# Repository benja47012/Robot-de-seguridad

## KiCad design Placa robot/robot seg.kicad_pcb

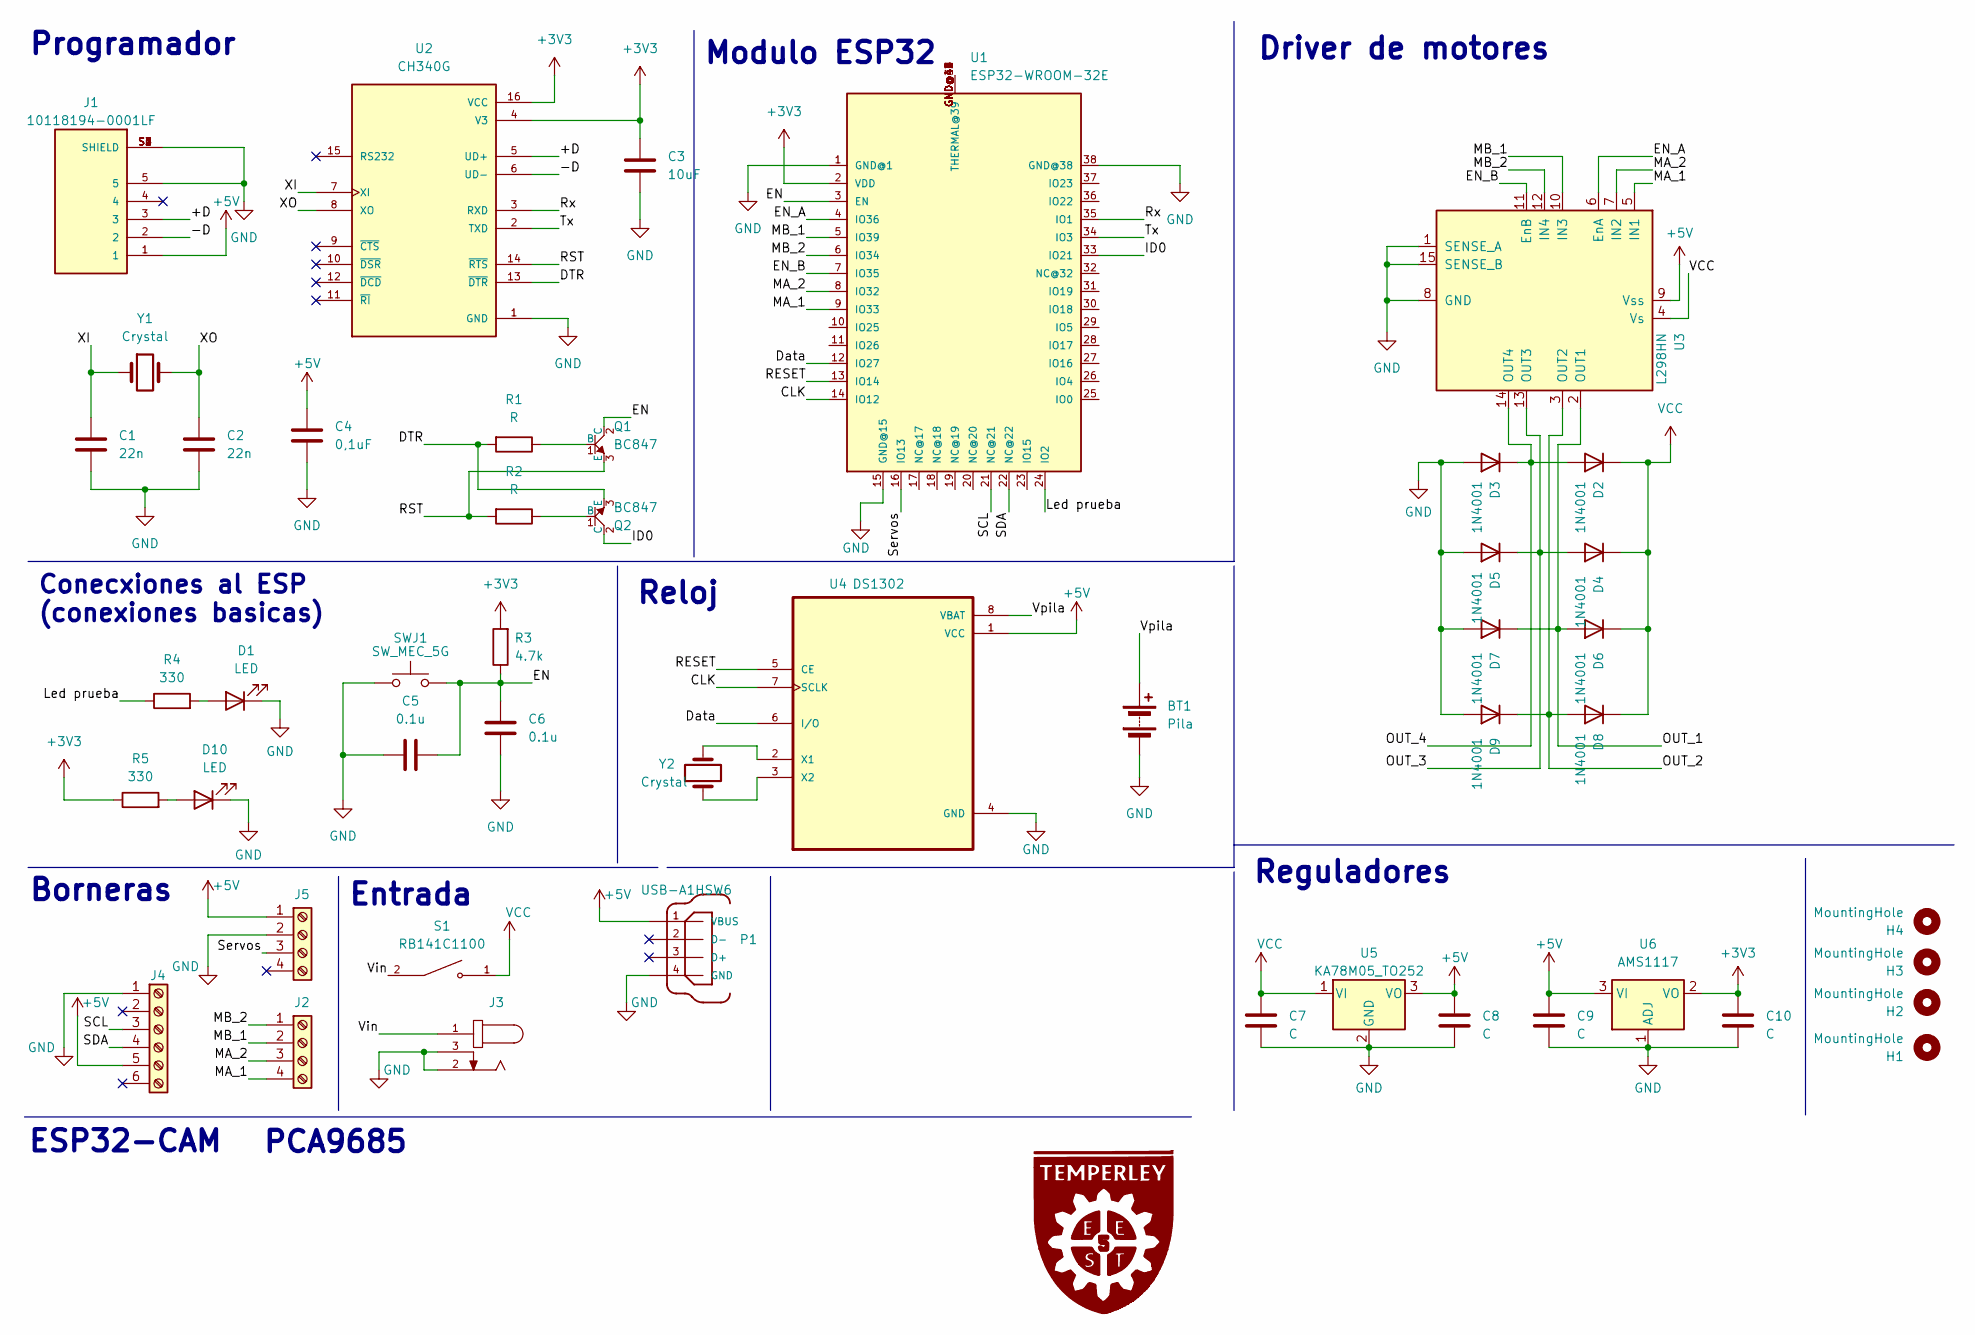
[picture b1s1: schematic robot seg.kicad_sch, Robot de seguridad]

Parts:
BT1: Pila; BatteryHolder_Keystone_105_1x2430
C1, C2: 22n; C_1206_3216Metric
C3: 10uF; C_1206_3216Metric
C4: 0,1uF; C_1206_3216Metric
C5, C6: 0.1u; C_1206_3216Metric
C7, C8, C9, C10: C; CP_Elec_10x12.5
D1, D10: LED; LED_1206_3216Metric
D2, D3, D4, D5, D6, D7, D8, D9: 1N4001; D_1812_4532Metric_Pad1.30x3.40mm_HandSolder
H1, H2, H3, H4: MountingHole; MountingHole_3.2mm_M3
J1: 10118194-0001LF; AMPHENOL_10118194-0001LF; PARTREV D
J2: Screw_Terminal_01x04; TerminalBlock_bornier-4_P5.08mm
J3: DCJ200-10-A-XX-K_REVA; GCT_DCJ200-10-A-XX-K_REVA; PARTREV A
J4: Controladora de servos; PinHeader_1x06_P2.54mm_Vertical
J5: Screw_Terminal_01x04; PinHeader_1x04_P2.54mm_Vertical
P1: USB-A1HSW6; OST_USB-A1HSW6
Q1, Q2: BC847; SOT-23-3
R1, R2: R; R_1210_3225Metric
R3: 4.7k; R_1210_3225Metric
R4, R5: 330; R_1210_3225Metric
S1: RB141C1100; SW_RB141C1100; PARTREV C
SWJ1: SW_MEC_5G; SW_SPST_Omron_B3F-315x_Angled
U1: ESP32-WROOM-32E
U2: CH340G; SOIC127P600X180-16N; PARTREV 2G
U3: L298HN; TO-220-15_P2.54x2.54mm_StaggerOdd_Lead4.58mm_Vertical
U4: DS1302; DIP794W47P254L991H457Q8
U5: KA78M05_TO252; TO-252-2
U6: AMS1117; SOT-223-3_TabPin2
Y1: Crystal; Crystal_HC49-4H_Vertical
Y2: Crystal; Crystal_C38-LF_D3.0mm_L8.0mm_Vertical

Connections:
+3V3: C3.1, C10.1, R3.2, R5.1, U1.2 (VDD), U2.4 (V3), U2.16 (VCC), U6.2 (VO)
+5V: C4.1, C8.1, C9.1, J1.1, J4.5, J5.1, P1.1 (VBUS), U3.9 (Vss), U4.1 (VCC), U5.3 (VO), U6.3 (VI)
/+D: J1.3, U2.5 (UD+)
/-D: J1.2, U2.6 (UD-)
/CLK: U1.14 (IO12), U4.7 (SCLK)
/DTR: Q2.3 (E), R1.2, U2.13 (~DTR)
/Data: U1.12 (IO27), U4.6 (I/O)
/EN: C5.2, C6.2, Q1.2 (C), R3.1, SWJ1.2 (B), U1.3 (EN)
/EN_A: U1.4 (IO36), U3.6 (EnA)
/EN_B: U1.7 (IO35), U3.11 (EnB)
/ID0: Q2.2 (C), U1.33 (IO21)
/Led prueba: R4.1, U1.24 (IO2)
/MA_1: J2.4, U1.9 (IO33), U3.5 (IN1)
/MA_2: J2.3, U1.8 (IO32), U3.7 (IN2)
/MB_1: J2.2, U1.5 (IO39), U3.10 (IN3)
/MB_2: J2.1, U1.6 (IO34), U3.12 (IN4)
/OUT_1: D6.2 (A), D7.1 (K), U3.2 (OUT1)
/OUT_2: D8.2 (A), D9.1 (K), U3.3 (OUT2)
/OUT_3: D4.2 (A), D5.1 (K), U3.13 (OUT3)
/OUT_4: D2.2 (A), D3.1 (K), U3.14 (OUT4)
/RESET: U1.13 (IO14), U4.5 (CE)
/RST: Q1.3 (E), R2.2, U2.14 (~RTS)
/Rx: U1.35 (IO1), U2.3 (RXD)
/SCL: J4.3, U1.21 (NC@21)
/SDA: J4.4, U1.22 (NC@22)
/Servos: J5.3, U1.16 (IO13)
/Tx: U1.34 (IO3), U2.2 (TXD)
/Vin: J3.1, S1.2
/Vpila: BT1.1 (+), U4.8 (VBAT)
/XI: C1.1, U2.7 (XI), Y1.1
/XO: C2.1, U2.8 (XO), Y1.2
GND: BT1.2 (-), C1.2, C2.2, C3.2, C4.2, C5.1, C6.1, C7.2, C8.2, C9.2, C10.2, D1.1 (K), D3.2 (A), D5.2 (A), D7.2 (A), D9.2 (A), D10.1 (K), J1.5, J1.S1 (SHIELD), J1.S2 (SHIELD), J1.S3 (SHIELD), J1.S4 (SHIELD), J1.S5 (SHIELD), J1.S6 (SHIELD), J3.2, J3.3, J4.1, J5.2, P1.4 (GND), SWJ1.1 (A), U1.1 (GND@1), U1.15 (GND@15), U1.38 (GND@38), U2.1 (GND), U3.1 (SENSE_A), U3.8 (GND), U3.15 (SENSE_B), U4.4 (GND), U5.2 (GND), U6.1 (ADJ)
unnamed: D1.2 (A), R4.2
unnamed: D10.2 (A), R5.2
unnamed: Q1.1 (B), R1.1
unnamed: Q2.1 (B), R2.1
unnamed: U1.GND@39 (THERMAL@39), U1.GND@40 (THERMAL@39), U1.GND@41 (THERMAL@39), U1.GND@42 (THERMAL@39), U1.GND@43 (THERMAL@39), U1.GND@44 (THERMAL@39), U1.GND@45 (THERMAL@39), U1.GND@46 (THERMAL@39), U1.GND@47 (THERMAL@39)
unnamed: U4.2 (X1), Y2.2
unnamed: U4.3 (X2), Y2.1
VCC: C7.1, D2.1 (K), D4.1 (K), D6.1 (K), D8.1 (K), S1.1, U3.4 (Vs), U5.1 (VI)

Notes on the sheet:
Reloj
Borneras
PCA9685
Driver de motores
ESP32-CAM
Entrada
Programador
Conecxiones al ESP (conexiones basicas)
Modulo ESP32
Reguladores

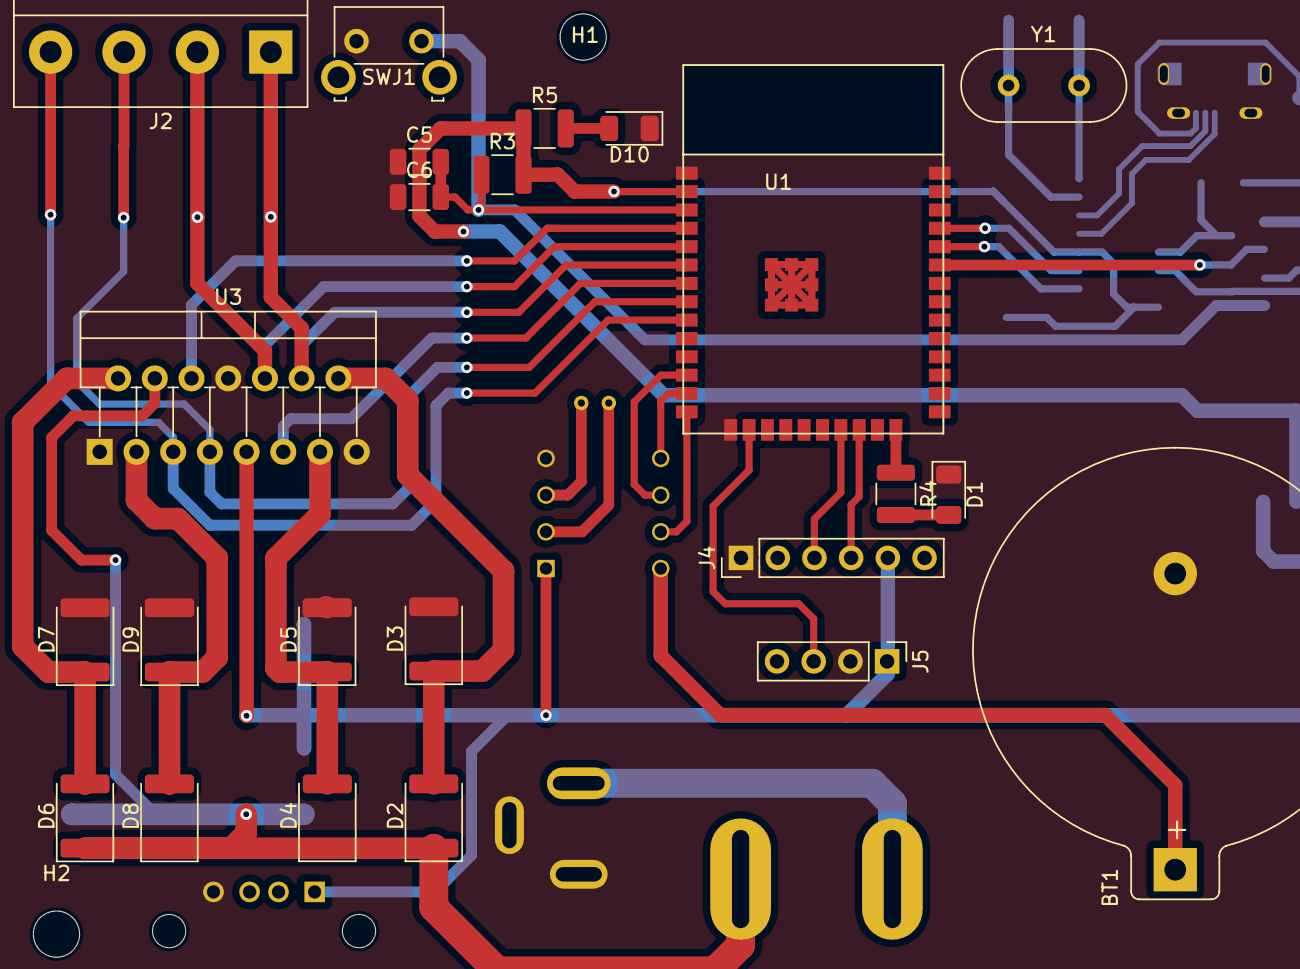
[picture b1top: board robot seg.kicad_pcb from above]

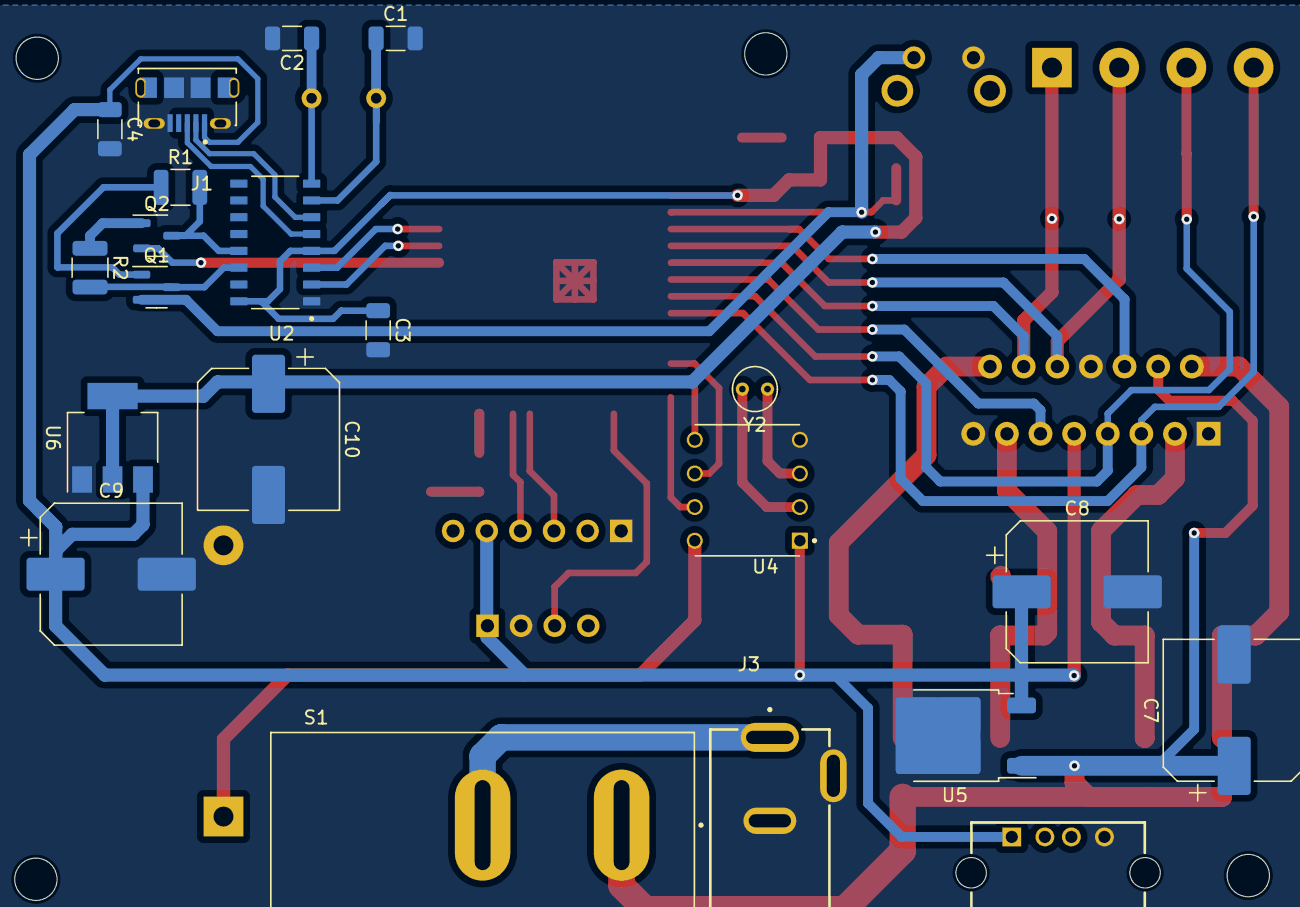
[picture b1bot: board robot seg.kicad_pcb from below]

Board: 2 copper layers, 48 parts (21 on the bottom side), 40 nets.

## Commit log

2023-10-18 mi primer commit
2023-11-01 v1 terminada
2023-11-03 V1-terminada-y-reducida
2023-11-03 V1-terminada-Reducida-y-mas-prolija
2023-11-03 V1-terminada-reducida-y-corregida
2023-11-07 Vercion-con-codigo-y-usb-para-cam
2023-11-15 V-final-con-codigo-y-placa
2023-11-15 V final con codigo
